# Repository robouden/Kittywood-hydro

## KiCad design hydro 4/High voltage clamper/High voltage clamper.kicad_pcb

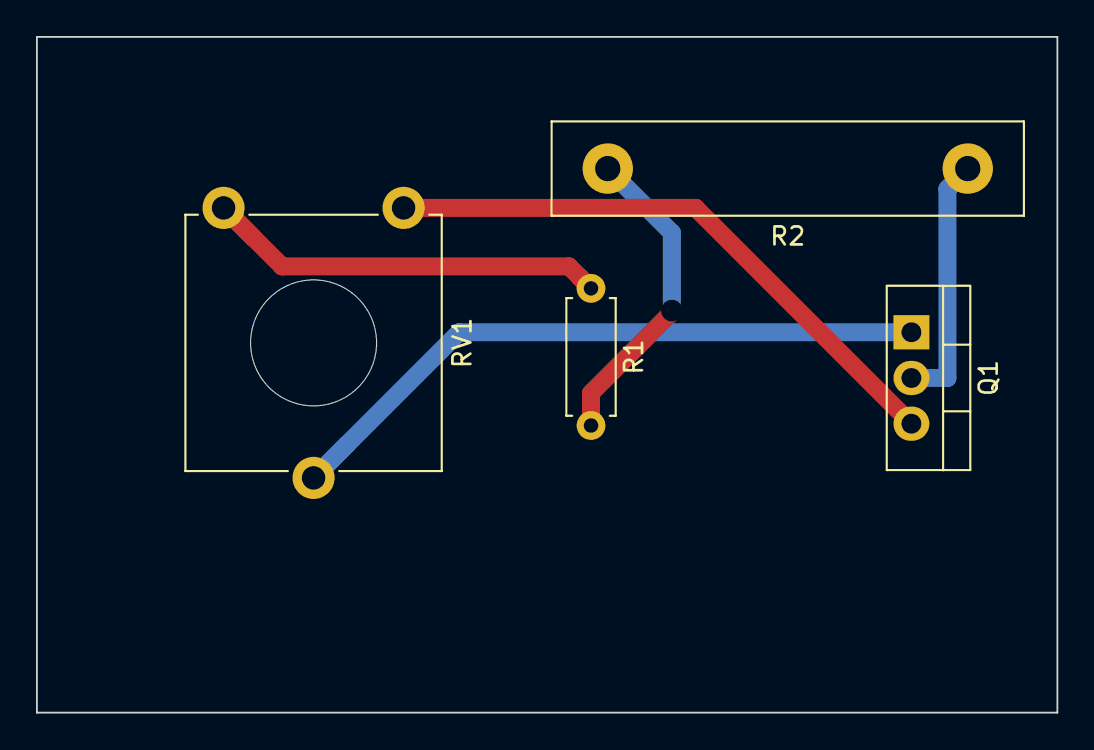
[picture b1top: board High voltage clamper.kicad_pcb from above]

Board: 2 copper layers, 56.7 x 37.5 mm, 4 parts (0 on the bottom side), 5 nets.

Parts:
Q1: IRF740; TO-220-3_Vertical
R1: 4.7M; R_Axial_DIN0207_L6.3mm_D2.5mm_P7.62mm_Horizontal
R2: 50 200watt; R_Box_L26.0mm_W5.0mm_P20.00mm
RV1: 1M; Potentiometer_ACP_CA14V-15_Vertical_Hole

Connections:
+VDC: R1.2, R2.2
-VDC: Q1.3 (S), RV1.3
unnamed: Q1.2 (D), R2.1
unnamed: Q1.1 (G), RV1.2
unnamed: R1.1, RV1.1

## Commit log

2022-12-10 init
2022-12-10 removed MAC OSX folder
2022-12-10 added runner-rpm
2022-12-14 added old pictures of hydro 2
2022-12-14 update with line for calculation of the angles and sizes of the hydro 2
2022-12-16 added more pictures
2022-12-18 Updated turgo.xls with 7mm nozzles
2023-01-11 Added dam and generator
2023-02-25 Added new files
2023-02-25 added tets for noseles
2023-12-17 added pcb
2023-12-17 Relink the files
2023-12-17 Updated clamp board
2023-12-25 Updated schematic
2024-01-08 Changed to fixed resistors
2024-01-10 Updated Nozzles
2024-02-03 Added 13mm and 14mm hydro nozzles
